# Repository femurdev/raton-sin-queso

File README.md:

# Ratón Sin Queso
*A mouse without cheese* 
- Onshape Document: https://cad.onshape.com/documents/3eceed79fd8189f0e7238951
# Where is it
A mouse whose hardware was hand-picked to squeeze as much performance out of it as possible. It is not light and not cheap, but I’ve got forearms so that don’t matter. As of writing this, I have it working over a wired connection but plan to implement Bluetooth protocols in the coming days.
## Who is it
I’m Femurdev, a recent high school graduate who’s excited about all things electronics, code, and research.
## Why is it
Back at the end of the school year, my trusty mouse broke. Since then, I have repaired it, but got me wondering if I could build a mouse with top of the line hardware and also make my own pcbs for it. I wanted to see if I could create an ergonomic gaming mouse for people with larger hands.
## Specs
8 side buttons, 3 indicator led, LMB, RMB, standard TTC encoder and MMB switch. Uses an nRF52 module from Seeed Studio for usb and Bluetooth compatibility.

## Usage & construction guide
- Print the 3D models in the repo, one of each. I made mine of PLA.
- Order the parts listed in the BOM.
- Construct the pcbs as according to the BOM.
- Place all parts on the bottom chassis.
- Glue the buttons to the top of them. They should remain about 2.2 mm above the shell when glued. 
- The flexibility of the PLA provides the spring back effect.
- Make connections as described in the kicad files. Connect your in place pcbs via the screw terminals. 
- If you’re using a TTC encoder as recommended, solder these jumpers.

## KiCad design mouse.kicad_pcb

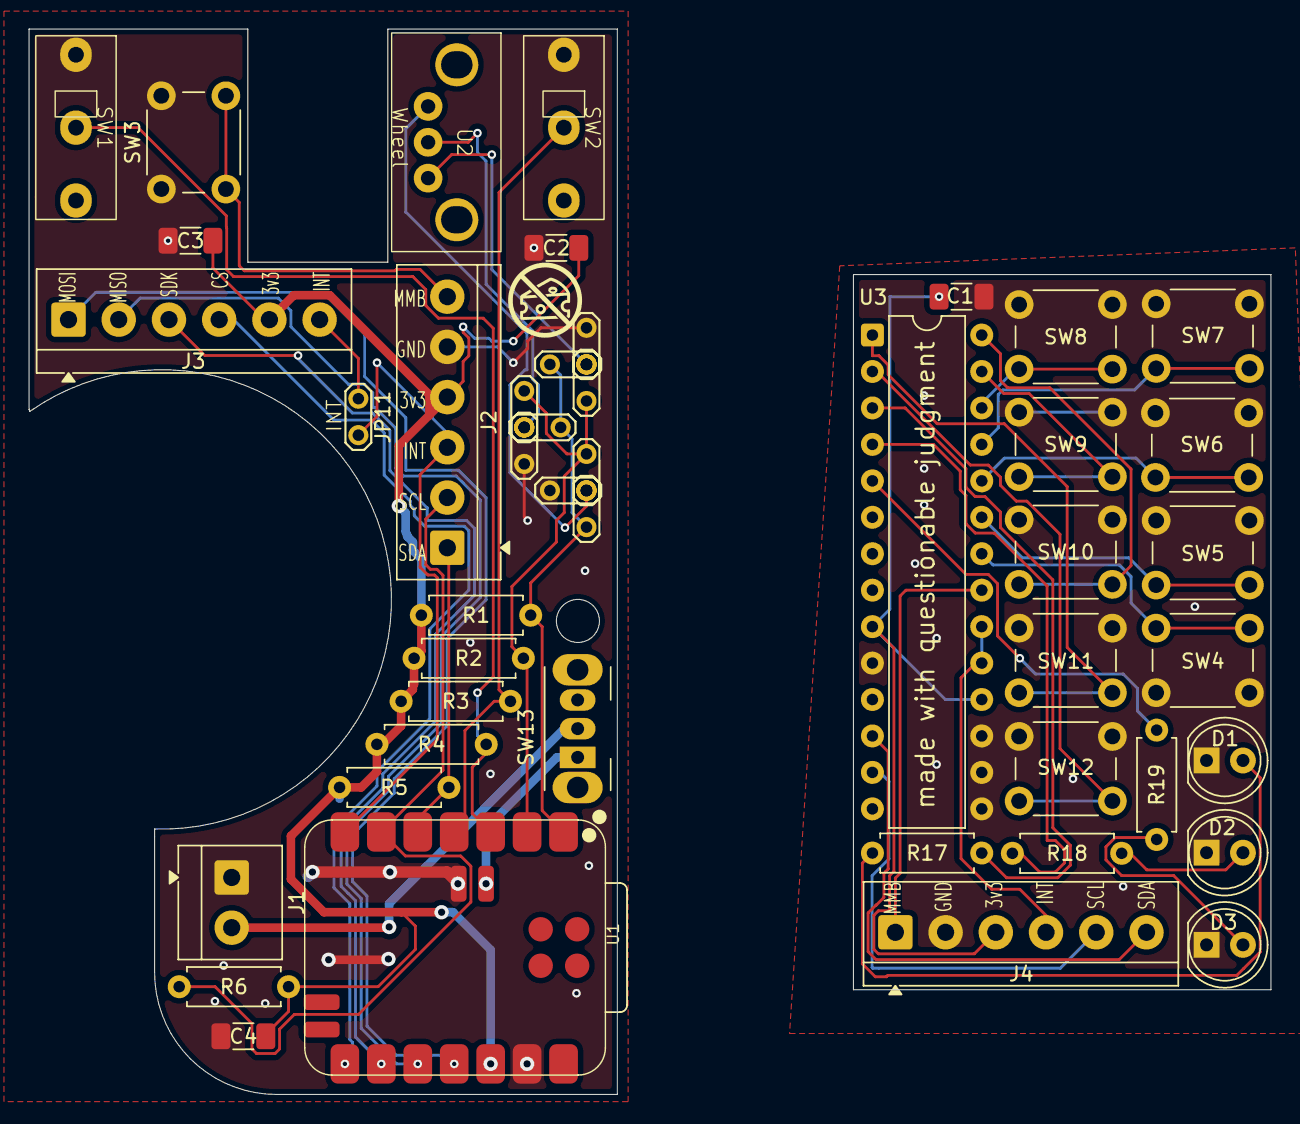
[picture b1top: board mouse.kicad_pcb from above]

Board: 2 copper layers, 86.6 x 74.2 mm, 46 parts (0 on the bottom side), 39 nets.

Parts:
C1, C2, C3, C4: .1μ; C_1206_3216Metric_Pad1.33x1.80mm_HandSolder
D1, D2, D3: LED; LED_D5.0mm
J1: Screw_Terminal_01x02; TerminalBlock_4Ucon_1x02_P3.50mm_Horizontal
J2, J3, J4: Screw_Terminal_01x06; TerminalBlock_4Ucon_1x06_P3.50mm_Horizontal
JP2, JP3, JP4, JP5, JP6, JP7, JP8, JP9, JP10, JP11: Jumper_2_Open; TestPoint_2Pads_Pitch2.54mm_Drill0.8mm
R1, R2, R3, R4, R5, R6: 10k; R_Axial_DIN0207_L6.3mm_D2.5mm_P7.62mm_Horizontal
R17, R18, R19: 2.2k; R_Axial_DIN0207_L6.3mm_D2.5mm_P7.62mm_Horizontal
SW1, SW2: Kailh_Mouse_Switch
SW3, SW4, SW5, SW6, SW7, SW8, SW9, SW10, SW11, SW12: SW_Push; SW_Kailh_6x6x7.3_Silent
SW13: SW_SPDT; SW_Slide_SPDT_Angled_CK_OS102011MA1Q
U1: XIAO-nRF52840-SMD
U2: TTC_Scrollwheel_Encoder
U3: MCP23017x-x-SP; DIP-28_W7.62mm

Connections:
+3V3: C1.1, C2.1, C3.1, C4.1, J2.4, J3.5, J4.3, R1.1, R2.1, R3.1, R4.1, R5.1, R6.1, U1.12 (3V3), U3.9 (V_{DD}), U3.18 (~RESET)
+BATT: SW13.1 (A), U1.20
/Button Board/int: J4.4, U3.19 (INTB), U3.20 (INTA)
/Button Board/mmb: J4.1, U3.21 (GPA0)
/Button Board/scl: J4.5, U3.13 (SDA)
/Button Board/sda: J4.6, U3.12 (SCK)
/Button Board/sideButtonMMB1/SIGNAL: SW4.2, U3.22 (GPA1)
/Button Board/sideButtonMMB2/SIGNAL: SW5.2, U3.23 (GPA2)
/Button Board/sideButtonMMB3/SIGNAL: SW6.2, U3.24 (GPA3)
/Button Board/sideButtonMMB4/SIGNAL: SW7.2, U3.25 (GPA4)
/Button Board/sideButtonMMB5/SIGNAL: SW8.2, U3.26 (GPA5)
/Button Board/sideButtonMMB6/SIGNAL: SW9.2, U3.27 (GPA6)
/Button Board/sideButtonMMB7/SIGNAL: SW10.2, U3.28 (GPA7)
/Button Board/sideButtonMMB8/SIGNAL: SW11.2, U3.1 (GPB0)
/Button Board/sideButtonMMB9/SIGNAL: SW12.2, U3.2 (GPB1)
/LMB: R4.2, SW1.2 (NO), U1.3 (P0.28_A2_D2)
/RMB: R3.2, SW2.2 (NO), U1.4 (P0.29_A3_D3)
/enc_a: JP3.1 (A), JP6.1 (A), JP9.1 (A), R1.2, U1.1 (P0.02_A0_D0)
/enc_b: JP4.1 (A), JP7.1 (A), JP10.1 (A), R2.2, U1.2 (P0.03_A1_D1)
/int: J2.3, JP11.1 (A), U1.7 (P1.11_D6_TX)
/mmb: J2.6, SW3.2
/scl: J2.2, R6.2, U1.6 (P0.05_A5_D5_SCL)
/sda: J2.1, R5.2, U1.5 (P0.04_A4_D4_SDA)
GND: C1.2, C2.2, C3.2, C4.2, D1.1 (K), D2.1 (K), D3.1 (K), J1.1, J2.5, J4.2, JP2.1 (A), JP5.1 (A), JP8.1 (A), SW1.1 (COM), SW2.1 (COM), SW3.1, SW4.1, SW5.1, SW6.1, SW7.1, SW8.1, SW9.1, SW10.1, SW11.1, SW12.1, U1.13 (GND), U1.19, U3.10 (V_{SS}), U3.15 (A0), U3.16 (A1), U3.17 (A2)
unnamed: D1.2 (A), R17.2
unnamed: D2.2 (A), R18.2
unnamed: D3.2 (A), R19.2
unnamed: J1.2, SW13.2 (B)
unnamed: J3.1, U1.11 (P1.15_D10_MOSI)
unnamed: J3.2, U1.10 (P1.14_D9_MISO)
unnamed: J3.3, U1.9 (P1.13_D8_SCK)
unnamed: J3.4, U1.8 (P1.12_D7_RX)
unnamed: J3.6, JP11.2 (B)
unnamed: JP2.2 (B), JP3.2 (B), JP4.2 (B), U2.1 (A)
unnamed: JP5.2 (B), JP6.2 (B), JP7.2 (B), U2.3 (COM)
unnamed: JP8.2 (B), JP9.2 (B), JP10.2 (B), U2.2 (B)
unnamed: R17.1, U3.3 (GPB2)
unnamed: R18.1, U3.4 (GPB3)
unnamed: R19.1, U3.5 (GPB4)

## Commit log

2026-06-21 Create README.md for Ratón Sin Queso project
    Added a detailed README for the Ratón Sin Queso project, including specifications, usage, and construction guide.
2026-06-21 Update README to remove Onshape Link
    Removed 'Onshape Link' from the README.
2026-06-21 Update README with image and project details
    Added an image to the README and updated project description.
2026-06-21 Fix formatting and update README content
2026-06-21 Enhance README with project details and links
    Updated README with additional information and links.
